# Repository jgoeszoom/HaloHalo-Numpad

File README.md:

# Halo-Halo Numpad!
A custom PCB implementation of a numpad that I designed for my girlfriend. 
(The name comes from a popular Filipino dessert; we thought it would be a fun name)

## Specifications
This numpad includes a 5x4 matrix of MX-style key switches along with a column of 
rotary encoders with a push-on switch built-in. 

At the moment, the board is still a WIP. The final board will include headers to attach a microcontroller that
will be chosen later. There should also be space for a small OLED/LCD screen. 

### To-do: 
	- [X] Choose a microcontroller to use
	- [X] Add headers for microcontroller chosen 
	- [] Update corresponding PDFs and images
	- [] Add space on PCB for the small screen

## Schematic

## PCB

## Render

## Bill-of-Materials

| References | Value | Footprint | Quantity |
| ---------- | ----- | --------- | -------- |
| C1-C20     | 0.1uF | 0805      | 20       |
| R1-R7, R9  | 4.7k  | Axial DIN0204 | 8    |
| R8         | 470   | Axial DIN0204 | 1    |
| D1-D20     | N/A   | SK6812 Mini | 20     | 
| D21-D40    | N/A   | SOD-123F  | 20       |
| SW1-SW20   | N/A   | Cherry MX | 20       |
| SW21-SW23  | Rotary| Alps EC11E| 3        |

C - Capacitors; R - Resistors; D - Diodes; SW - Switches

Included in the BOM directory is an HTML for an interactive BOM generated by a plugin in KiCAD. 
When this is opened, a rendered HTML page shows all the items on the PCB as well as their location
and values and footprints. It's a nice side by side view of a BOM and the PCB.

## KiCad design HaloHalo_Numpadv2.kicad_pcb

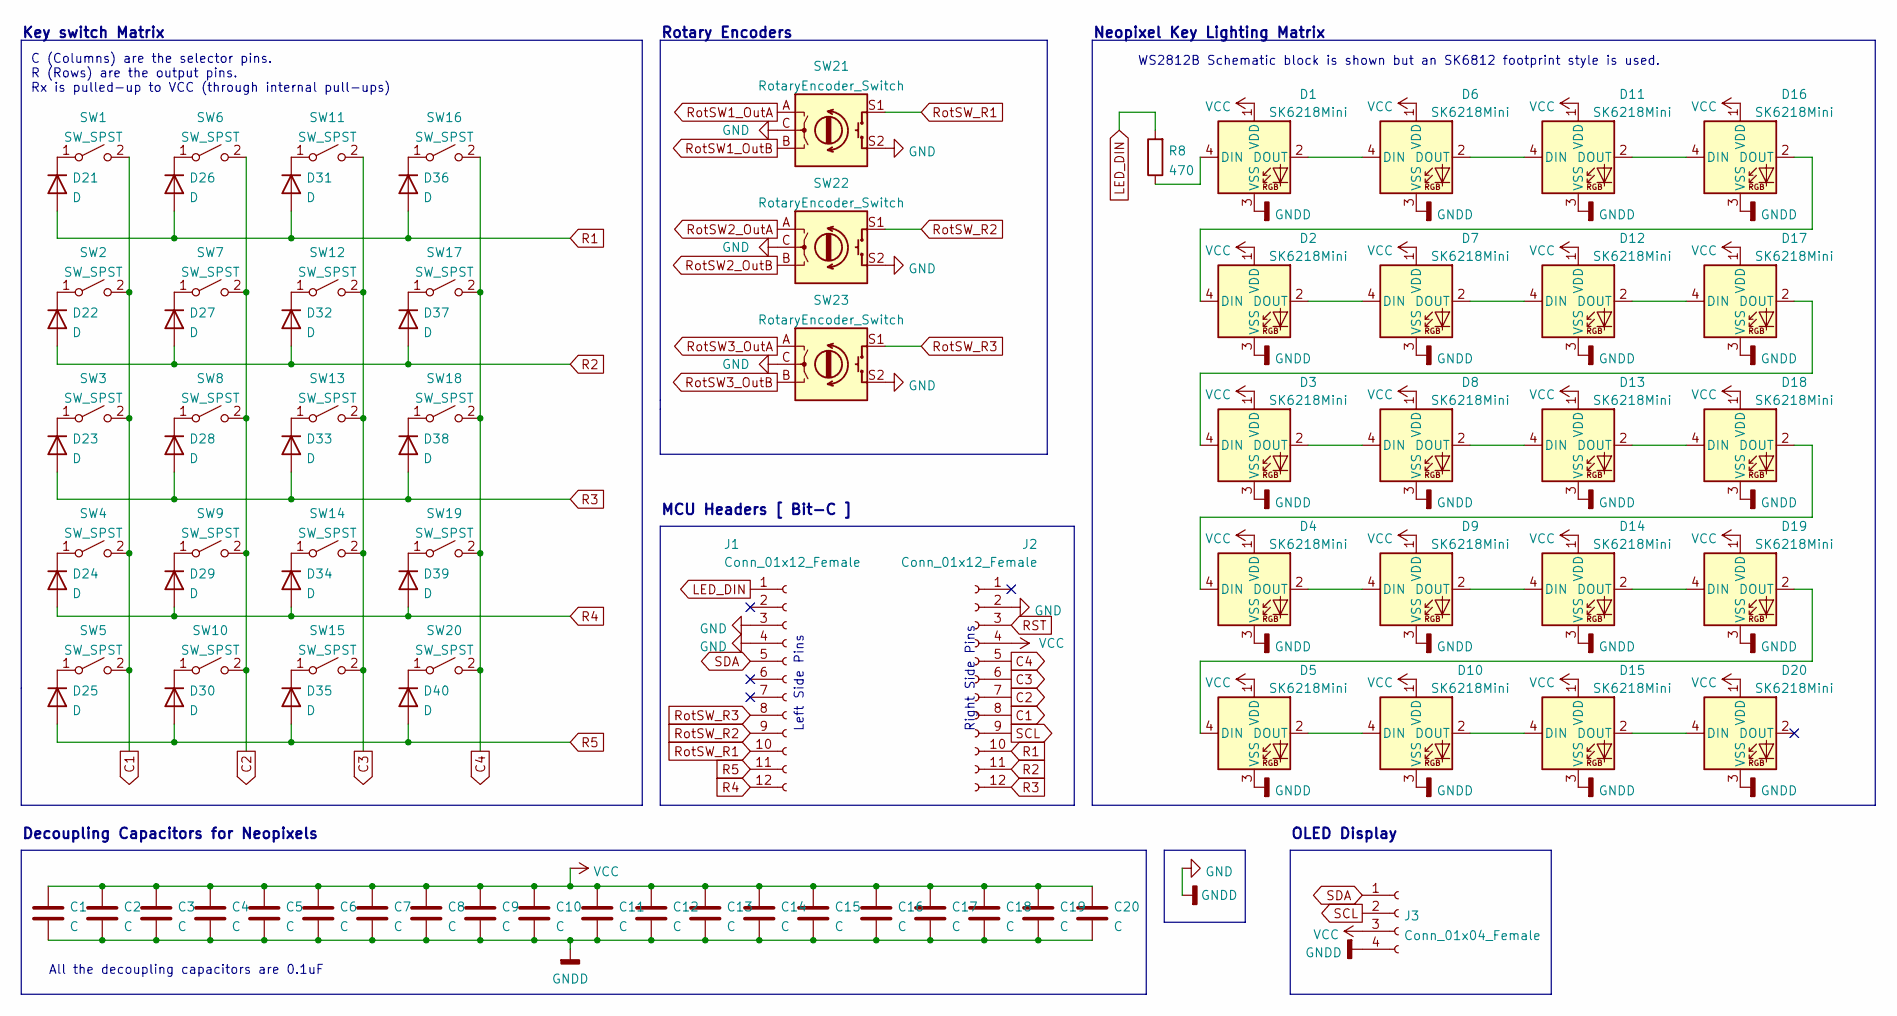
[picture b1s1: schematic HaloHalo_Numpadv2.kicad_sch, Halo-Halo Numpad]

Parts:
C1: C; C_0805_2012Metric_Pad1.18x1.45mm_HandSolder; MFR. Part Number FS055C104K4Z2A; LCSC Part Number C444732
C2, C3, C4, C5, C6, C7, C8, C9, C10, C11, C12, C13, C14, C15, C16, C17, C18, C19, C20: C; C_0805_2012Metric_Pad1.18x1.45mm_HandSolder
D1, D2, D3, D4, D5, D6, D7, D8, D9, D10, D11, D12, D13, D14, D15, D16, D17, D18, D19, D20: SK6218Mini; SK6812Mini
D21, D22, D23, D24, D25, D26, D27, D28, D29, D30, D31, D32, D33, D34, D35, D36, D37, D38, D39, D40: D; D_SOD-123F; MFR. Part Number SM4007PL; LCSC Part Number C64898
J1, J2: Conn_01x12_Female; PinSocket_1x12_P2.54mm_Vertical
J3: Conn_01x04_Female; PinSocket_1x04_P2.54mm_Vertical
R8: 470; R_Axial_DIN0204_L3.6mm_D1.6mm_P5.08mm_Horizontal
SW1, SW2, SW3, SW4, SW5, SW6, SW7, SW8, SW9, SW10, SW11, SW12, SW13, SW14, SW15, SW16, SW17, SW18, SW19, SW20: SW_SPST; SW_Cherry_MX_1.00u_PCB
SW21, SW22, SW23: RotaryEncoder_Switch; RotaryEncoder_Alps_EC11E-Switch_Vertical_H20mm

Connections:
C1: J2.8, SW1.2 (B), SW2.2 (B), SW3.2 (B), SW4.2 (B), SW5.2 (B)
C2: J2.7, SW6.2 (B), SW7.2 (B), SW8.2 (B), SW9.2 (B), SW10.2 (B)
C3: J2.6, SW11.2 (B), SW12.2 (B), SW13.2 (B), SW14.2 (B), SW15.2 (B)
C4: J2.5, SW16.2 (B), SW17.2 (B), SW18.2 (B), SW19.2 (B), SW20.2 (B)
GND: C1.2, C2.2, C3.2, C4.2, C5.2, C6.2, C7.2, C8.2, C9.2, C10.2, C11.2, C12.2, C13.2, C14.2, C15.2, C16.2, C17.2, C18.2, C19.2, C20.2, D1.3 (VSS), D2.3 (VSS), D3.3 (VSS), D4.3 (VSS), D5.3 (VSS), D6.3 (VSS), D7.3 (VSS), D8.3 (VSS), D9.3 (VSS), D10.3 (VSS), D11.3 (VSS), D12.3 (VSS), D13.3 (VSS), D14.3 (VSS), D15.3 (VSS), D16.3 (VSS), D17.3 (VSS), D18.3 (VSS), D19.3 (VSS), D20.3 (VSS), J1.3, J1.4, J2.2, J3.4, SW21.C, SW21.S2, SW22.C, SW22.S2, SW23.C, SW23.S2
LED_DIN: J1.1, R8.2
unnamed: D1.2 (DOUT), D6.4 (DIN)
unnamed: D1.4 (DIN), R8.1
unnamed: D2.2 (DOUT), D7.4 (DIN)
unnamed: D3.2 (DOUT), D8.4 (DIN)
unnamed: D4.2 (DOUT), D9.4 (DIN)
unnamed: D10.2 (DOUT), D15.4 (DIN)
unnamed: D5.2 (DOUT), D10.4 (DIN)
unnamed: D11.2 (DOUT), D16.4 (DIN)
unnamed: D6.2 (DOUT), D11.4 (DIN)
unnamed: D12.2 (DOUT), D17.4 (DIN)
unnamed: D7.2 (DOUT), D12.4 (DIN)
unnamed: D13.2 (DOUT), D18.4 (DIN)
unnamed: D8.2 (DOUT), D13.4 (DIN)
unnamed: D14.2 (DOUT), D19.4 (DIN)
unnamed: D9.2 (DOUT), D14.4 (DIN)
unnamed: D15.2 (DOUT), D20.4 (DIN)
unnamed: D2.4 (DIN), D16.2 (DOUT)
unnamed: D3.4 (DIN), D17.2 (DOUT)
unnamed: D4.4 (DIN), D18.2 (DOUT)
unnamed: D5.4 (DIN), D19.2 (DOUT)
unnamed: D21.1 (K), SW1.1 (A)
unnamed: D22.1 (K), SW2.1 (A)
unnamed: D23.1 (K), SW3.1 (A)
unnamed: D24.1 (K), SW4.1 (A)
unnamed: D25.1 (K), SW5.1 (A)
unnamed: D26.1 (K), SW6.1 (A)
unnamed: D27.1 (K), SW7.1 (A)
unnamed: D28.1 (K), SW8.1 (A)
unnamed: D29.1 (K), SW9.1 (A)
unnamed: D30.1 (K), SW10.1 (A)
unnamed: D31.1 (K), SW11.1 (A)
unnamed: D32.1 (K), SW12.1 (A)
unnamed: D33.1 (K), SW13.1 (A)
unnamed: D34.1 (K), SW14.1 (A)
unnamed: D35.1 (K), SW15.1 (A)
unnamed: D36.1 (K), SW16.1 (A)
unnamed: D37.1 (K), SW17.1 (A)
unnamed: D38.1 (K), SW18.1 (A)
unnamed: D39.1 (K), SW19.1 (A)
unnamed: D40.1 (K), SW20.1 (A)
R1: D21.2 (A), D26.2 (A), D31.2 (A), D36.2 (A), J2.10
R2: D22.2 (A), D27.2 (A), D32.2 (A), D37.2 (A), J2.11
R3: D23.2 (A), D28.2 (A), D33.2 (A), D38.2 (A), J2.12
R4: D24.2 (A), D29.2 (A), D34.2 (A), D39.2 (A), J1.12
R5: D25.2 (A), D30.2 (A), D35.2 (A), D40.2 (A), J1.11
RST: J2.3
RotSW1_OutA: SW21.A
RotSW1_OutB: SW21.B
RotSW2_OutA: SW22.A
RotSW2_OutB: SW22.B
RotSW3_OutA: SW23.A
RotSW3_OutB: SW23.B
RotSW_R1: J1.10, SW21.S1
RotSW_R2: J1.9, SW22.S1
RotSW_R3: J1.8, SW23.S1
SCL: J2.9, J3.2
SDA: J1.5, J3.1
VCC: C1.1, C2.1, C3.1, C4.1, C5.1, C6.1, C7.1, C8.1, C9.1, C10.1, C11.1, C12.1, C13.1, C14.1, C15.1, C16.1, C17.1, C18.1, C19.1, C20.1, D1.1 (VDD), D2.1 (VDD), D3.1 (VDD), D4.1 (VDD), D5.1 (VDD), D6.1 (VDD), D7.1 (VDD), D8.1 (VDD), D9.1 (VDD), D10.1 (VDD), D11.1 (VDD), D12.1 (VDD), D13.1 (VDD), D14.1 (VDD), D15.1 (VDD), D16.1 (VDD), D17.1 (VDD), D18.1 (VDD), D19.1 (VDD), D20.1 (VDD), J2.4, J3.3

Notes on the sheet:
Left Side Pins
Key switch Matrix
MCU Headers [ Bit-C ]
Right Side Pins
Rotary Encoders
WS2812B Schematic block is shown but an SK6812 footprint style is used.
OLED Display
C (Columns) are the selector pins. R (Rows) are the output pins. Rx is pulled-up to VCC (through internal pull-ups)
Neopixel Key Lighting Matrix
All the decoupling capacitors are 0.1uF
Decoupling Capacitors for Neopixels

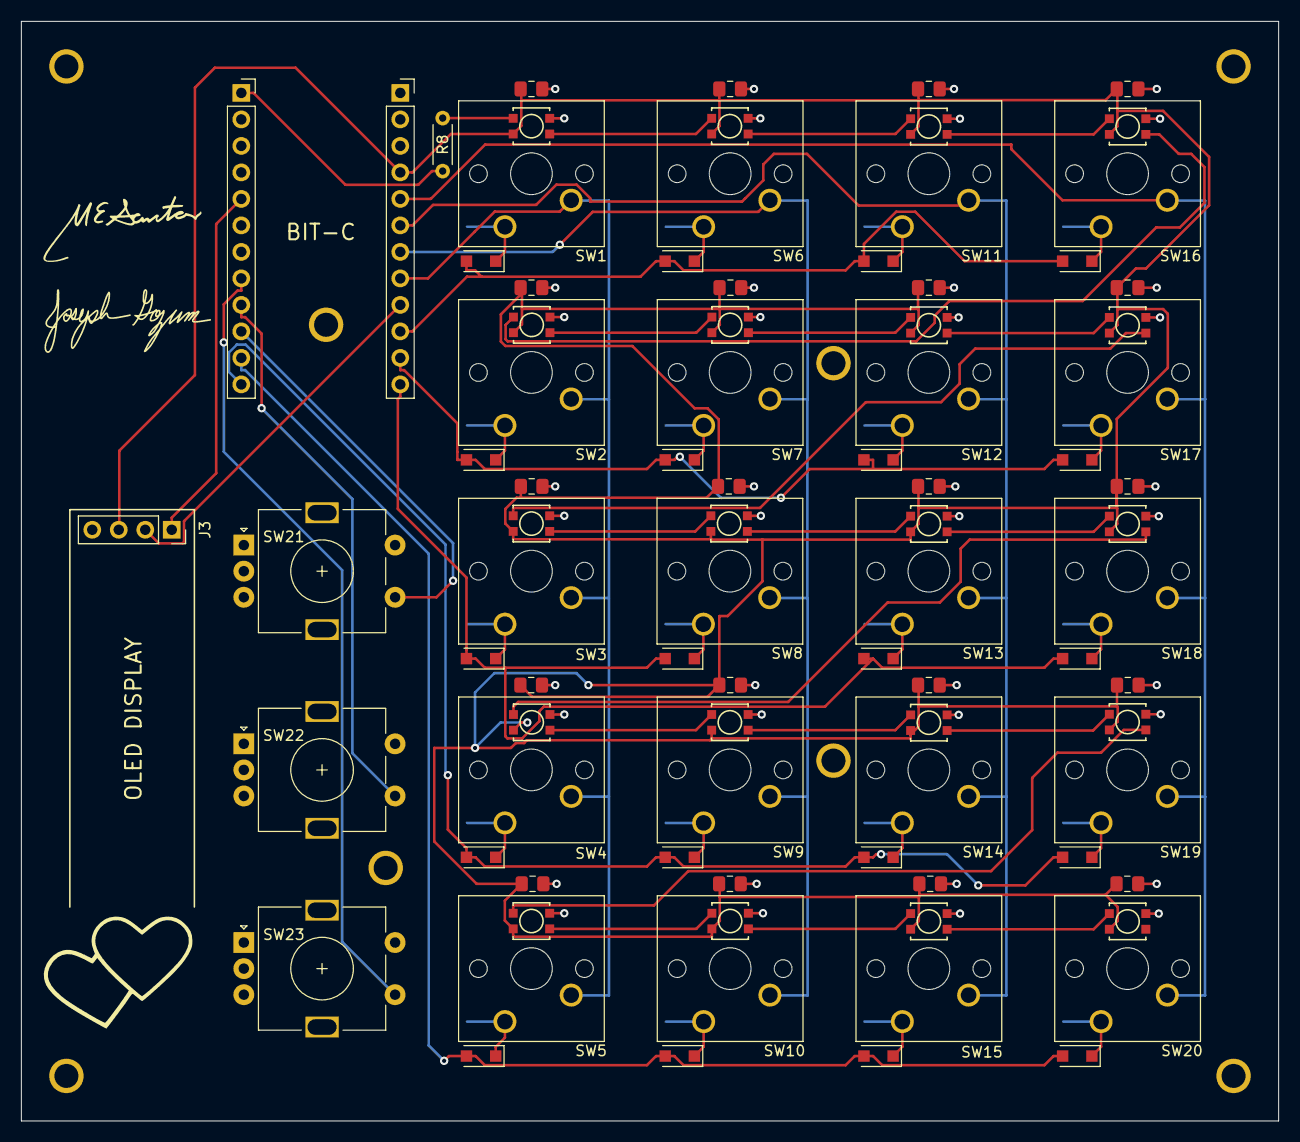
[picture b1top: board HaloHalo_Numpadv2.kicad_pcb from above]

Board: 2 copper layers, 120.5 x 105.4 mm, 99 parts (0 on the bottom side), 57 nets.

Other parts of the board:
G1, G2, G3: LOGO
HOLE5, HOLE5#2, HOLE5#3, HOLE5#4, HOLE5#5, HOLE5#6, HOLE5#7, HOLE5#8: MountingHole_4mm; MountingHole_M2
Hearts: LOGO

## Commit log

2022-01-30 Changed colors of PCB assembly files in Board2Pdf. Placed all diodes on PCB.
2022-01-30 Added .gitignore
2022-01-30 Flipped orientation of key switches. Began initial trace routing.
2022-01-30 Added a README.md
2022-01-30 Added more sections to README.md
2022-01-30 Updated schematic fields. Uploaded PDFs and images of schematic.
2022-01-30 Fixed list in README
2022-01-30 Added PCB PDFs and images
2022-01-30 Added PCB Board PDF and png
2022-01-30 Added PCB image to README
2022-01-30 Fixed image link in README for PCB section
2022-01-30 Added PCB render image
2022-01-30 Added Rendered PCB image to README.
2022-01-31 Added interactive BOM HTML and BOM section in READ
2022-01-31 Added BOM section to README. Link to interactive BOM
2022-01-31 Fixed link to BOM in README
2022-01-31 Attempt #2 to fix BOM link in README
2022-01-31 Removed link to HTML in BOM section of README. Just described what it is instead.
2022-02-02 Start ignorning SVGs and updated PDF and PNG of Numpad Schematic
2022-02-02 Fixed wiring of active low switch matrix in Eschema. Updated corresponding PNG and PDF file for schematic.
2022-02-03 Updated Schematic and PCB to include headers for OLED display. Need to update corresponding PDFs and images.
2022-02-03 Updated README Todo section.
2022-02-04 Added OLED display headers
2022-02-04 Added silkscreen images to PCB
2022-02-04 Updated all image files and PDFs
2022-02-04 Moved position of display headers in PCB. Started tracking gerbers.zip
